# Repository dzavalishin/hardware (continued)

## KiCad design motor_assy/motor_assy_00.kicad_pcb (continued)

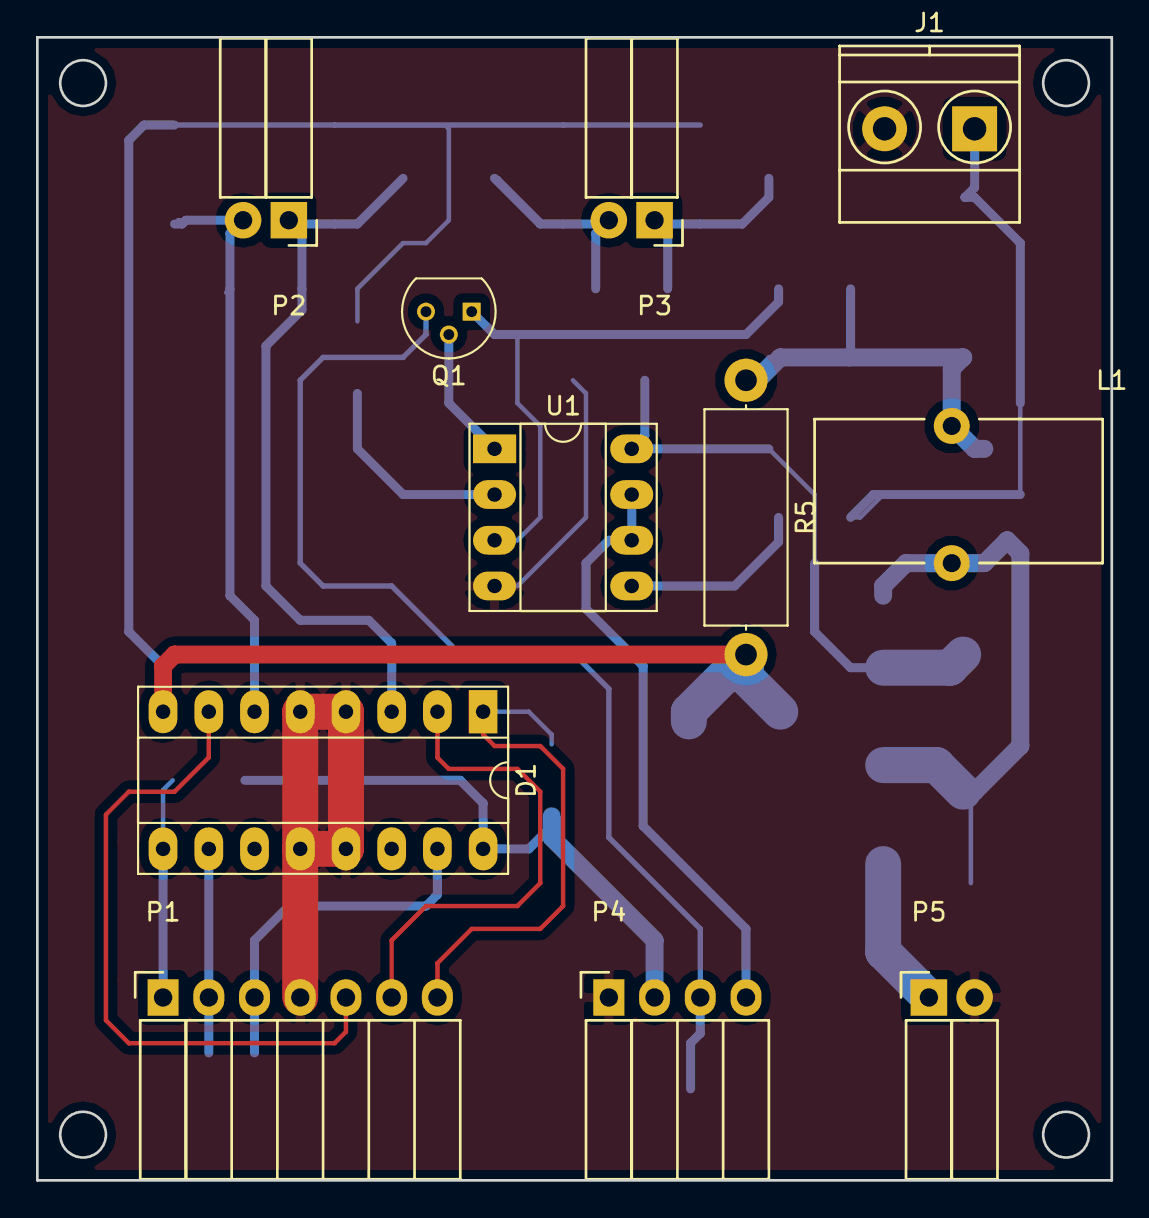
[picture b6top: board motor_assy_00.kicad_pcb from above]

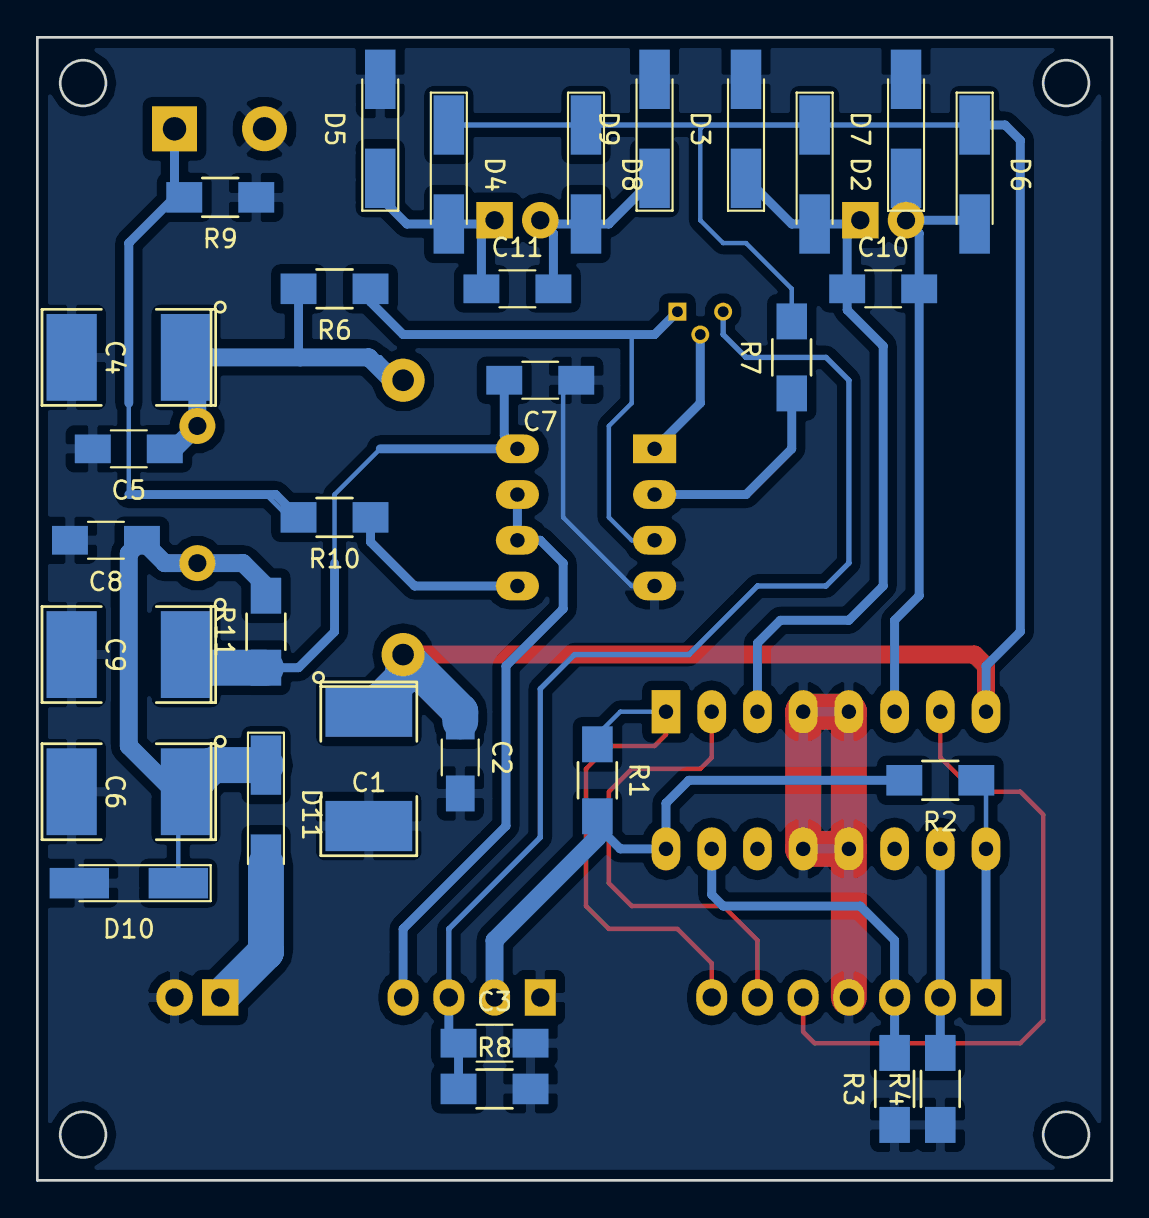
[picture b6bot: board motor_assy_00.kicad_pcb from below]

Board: 2 copper layers, 59.7 x 63.5 mm, 42 parts (31 on the bottom side), 24 nets.

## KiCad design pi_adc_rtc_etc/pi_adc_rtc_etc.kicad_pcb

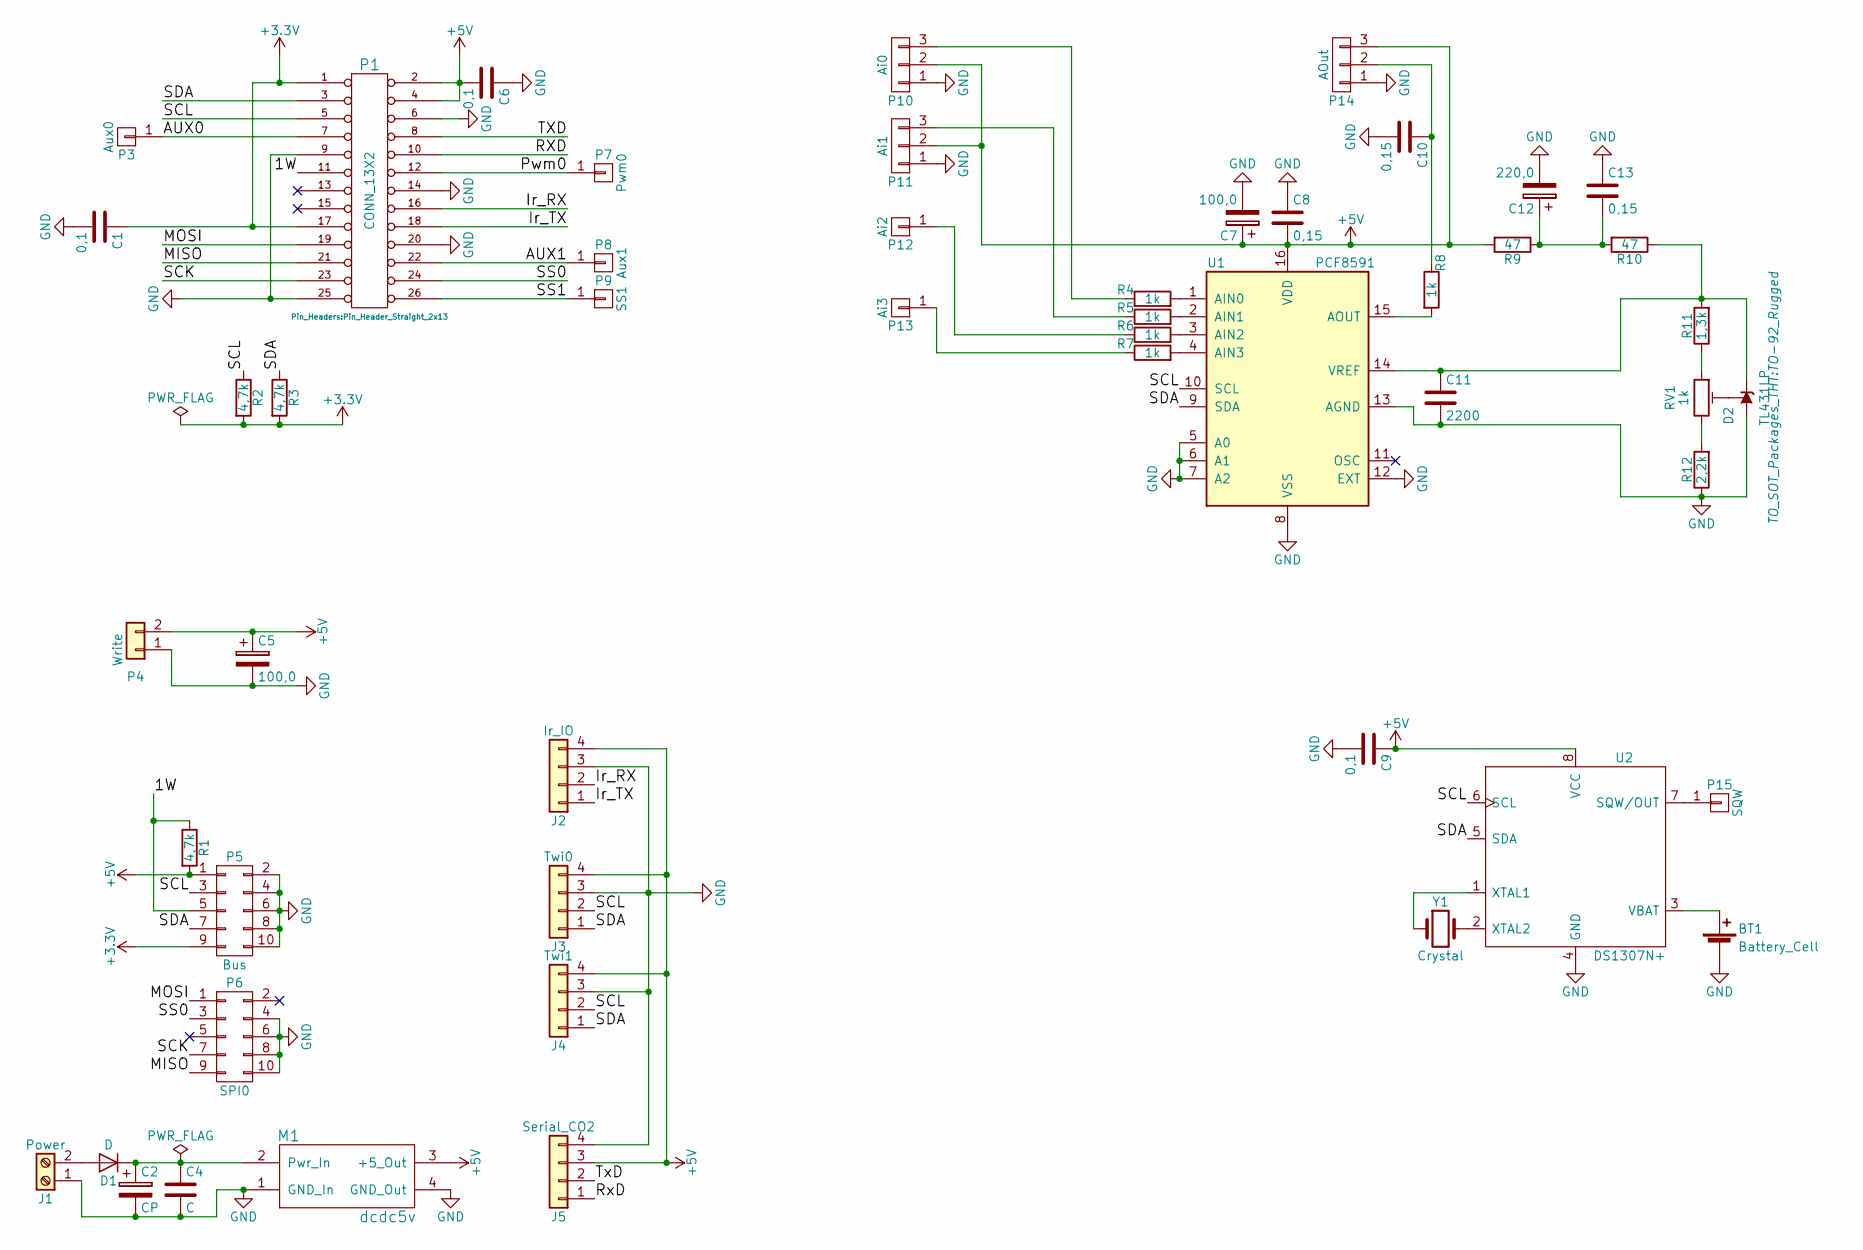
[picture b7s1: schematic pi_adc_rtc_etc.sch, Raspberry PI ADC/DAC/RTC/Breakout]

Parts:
BT1: Battery_Cell; WireConnection_2.00mmDrill
C1, C6, C9: 0,1; C_1206_HandSoldering
C2: CP; CP_Tantalum_Case-B_EIA-3528-21_Hand
C4: C; C_1206_HandSoldering
C5: 100,0; CP_Radial_D10.0mm_P2.50mm
C7: 100,0; CP_Tantalum_Case-B_EIA-3528-21_Hand
C8, C10, C13: 0,15; C_1206_HandSoldering
C11: 2200; C_1206_HandSoldering
C12: 220,0; CP_Tantalum_Case-B_EIA-3528-21_Hand
D1: D; D_MELF_Handsoldering
D2: TL431LP; TO-92_Rugged
J1: Power; TerminalBlock_bornier-2_P5.08mm
J2: Ir_IO; Pin_Header_Straight_1x04_Pitch2.54mm
J3: Twi0; Pin_Header_Straight_1x04_Pitch2.54mm
J4: Twi1; Pin_Header_Straight_1x04_Pitch2.54mm
J5: Serial_CO2; Pin_Header_Straight_1x04_Pitch2.54mm
M1: dcdc5v
P1: CONN_13X2; Pin_Header_Straight_2x13
P3: Aux0; Pin_Header_Straight_1x01_Pitch2.54mm
P4: Write; TerminalBlock_bornier-2_P5.08mm
P5: Bus; Pin_Header_Straight_2x05_Pitch2.54mm
P6: SPI0; Pin_Header_Straight_2x05_Pitch2.54mm
P7: Pwm0; Pin_Header_Straight_1x01_Pitch2.54mm
P8: Aux1; Pin_Header_Straight_1x01_Pitch2.54mm
P9: SS1; Pin_Header_Straight_1x01_Pitch2.54mm
P10: Ai0; Pin_Header_Straight_1x03_Pitch2.54mm
P11: Ai1; Pin_Header_Straight_1x03_Pitch2.54mm
P12: Ai2; Pin_Header_Straight_1x01_Pitch2.54mm
P13: Ai3; Pin_Header_Straight_1x01_Pitch2.54mm
P14: AOut; Pin_Header_Straight_1x03_Pitch2.54mm
P15: SQW; Pin_Header_Straight_1x01_Pitch2.54mm
R1, R2, R3: 4,7k; R_1206_HandSoldering
R4, R5, R6, R7, R8: 1k; R_1206_HandSoldering
R9, R10: 47; R_1206_HandSoldering
R11: 1,3k; R_1206_HandSoldering
R12: 2,2k; R_1206_HandSoldering
RV1: 1k; Potentiometer_Trimmer_Bourns_3296W
U1: PCF8591; DIP-16_W7.62mm_LongPads
U2: DS1307N+; DIP-8_W7.62mm_LongPads
Y1: Crystal; Crystal_AT310_d3.0mm_l10.0mm_Horizontal

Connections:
+3V3: C1.1, P1.1, P1.17, P5.9, R2.2, R3.2
+5V: C5.1, C6.2, C7.1, C8.2, C9.1, J2.4, J3.4, J4.4, J5.3, M1.3 (+5_Out), P1.2, P1.4, P4.2, P5.1, P10.2, P11.2, P14.3, R1.2, R9.2, U1.16 (VDD), U2.8 (VCC)
/1W: P1.11, P5.5, R1.1
/AUX0: P1.7, P3.1
/AUX1: P1.22, P8.1
/Ir_RX: J2.2, P1.16
/Ir_TX: J2.1, P1.18
/MISO: P1.21, P6.9
/MOSI: P1.19, P6.1
/Pwm0: P1.12, P7.1
/RXD: J5.1, P1.10
/SCK: P1.23, P6.7
/SCL: J3.2, J4.2, P1.5, P5.3, R2.1, U1.10 (SCL), U2.6 (SCL)
/SDA: J3.1, J4.1, P1.3, P5.7, R3.1, U1.9 (SDA), U2.5 (SDA)
/SS0: P1.24 (P20), P6.3
/SS1: P1.26 (P22), P9.1
/TXD: J5.2, P1.8
GND: BT1.2 (-), C1.2, C2.2, C4.2, C5.2, C6.1, C7.2, C8.1, C9.2, C10.2, C11.2, C12.2, C13.1, D2.2 (A), J1.1, J2.3, J3.3, J4.3, J5.4, M1.1 (GND_In), M1.4 (GND_Out), P1.6, P1.9, P1.14, P1.20, P1.25 (P24), P4.1, P5.2, P5.4, P5.6, P5.8, P5.10, P6.4, P6.6, P6.8, P6.10, P10.1, P11.1, P14.1, R12.1, U1.5 (A0), U1.6 (A1), U1.7 (A2), U1.8 (VSS), U1.12 (EXT), U1.13 (AGND), U2.4 (GND)
unnamed: BT1.1 (+), U2.3 (VBAT)
unnamed: C2.1, C4.1, D1.1 (K), M1.2 (Pwr_In)
unnamed: C10.1, P14.2, R8.1
unnamed: C11.1, D2.3 (K), R10.1, R11.2, U1.14 (VREF)
unnamed: C12.1, C13.2, R9.1, R10.2
unnamed: D1.2 (A), J1.2
unnamed: D2.1 (REF), RV1.2
unnamed: P10.3, R4.1
unnamed: P11.3, R5.1
unnamed: P12.1, R6.1
unnamed: P13.1, R7.1
unnamed: P15.1, U2.7 (SQW/OUT)
unnamed: R4.2, U1.1 (AIN0)
unnamed: R5.2, U1.2 (AIN1)
unnamed: R6.2, U1.3 (AIN2)
unnamed: R7.2, U1.4 (AIN3)
unnamed: R8.2, U1.15 (AOUT)
unnamed: R11.1, RV1.1
unnamed: R12.2, RV1.3
unnamed: U2.1 (XTAL1), Y1.1
unnamed: U2.2 (XTAL2), Y1.2

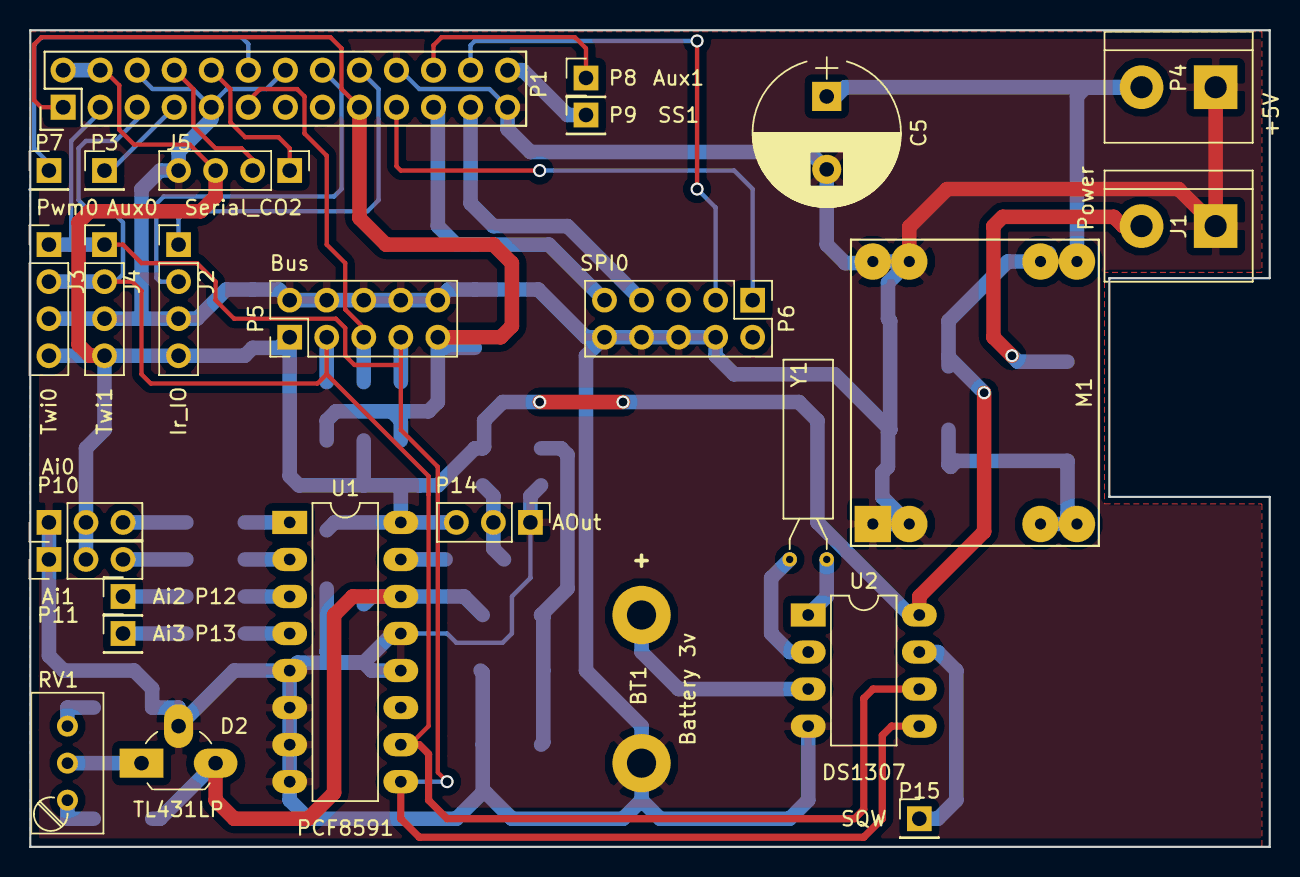
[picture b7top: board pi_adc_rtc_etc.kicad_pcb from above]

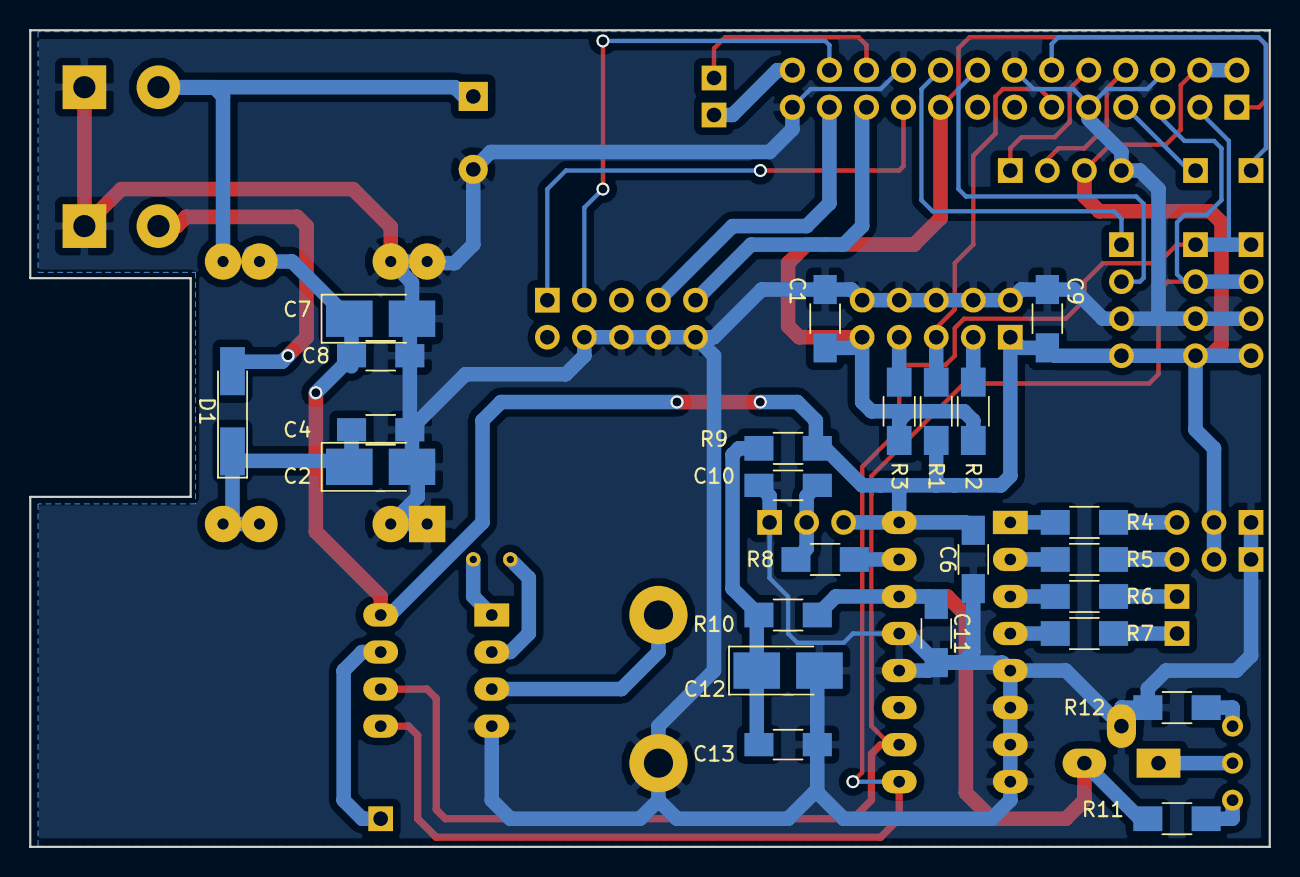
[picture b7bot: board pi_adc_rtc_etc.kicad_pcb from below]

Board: 2 copper layers, 85.0 x 56.0 mm, 51 parts (24 on the bottom side), 39 nets.
